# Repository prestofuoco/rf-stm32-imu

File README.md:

# rf-stm32-imu
4-layer (sig-gnd-gnd-sig) PCB with STM32F4, ICM20948, NRF24L01, USB-C, and 2.4GHz PCB trace antenna from TI's AN043. USB and RF traces are impedance matched/controlled to 90 ohms and 50 ohms respectively.

Antenna: https://www.ti.com/lit/an/swra117d/swra117d.pdf

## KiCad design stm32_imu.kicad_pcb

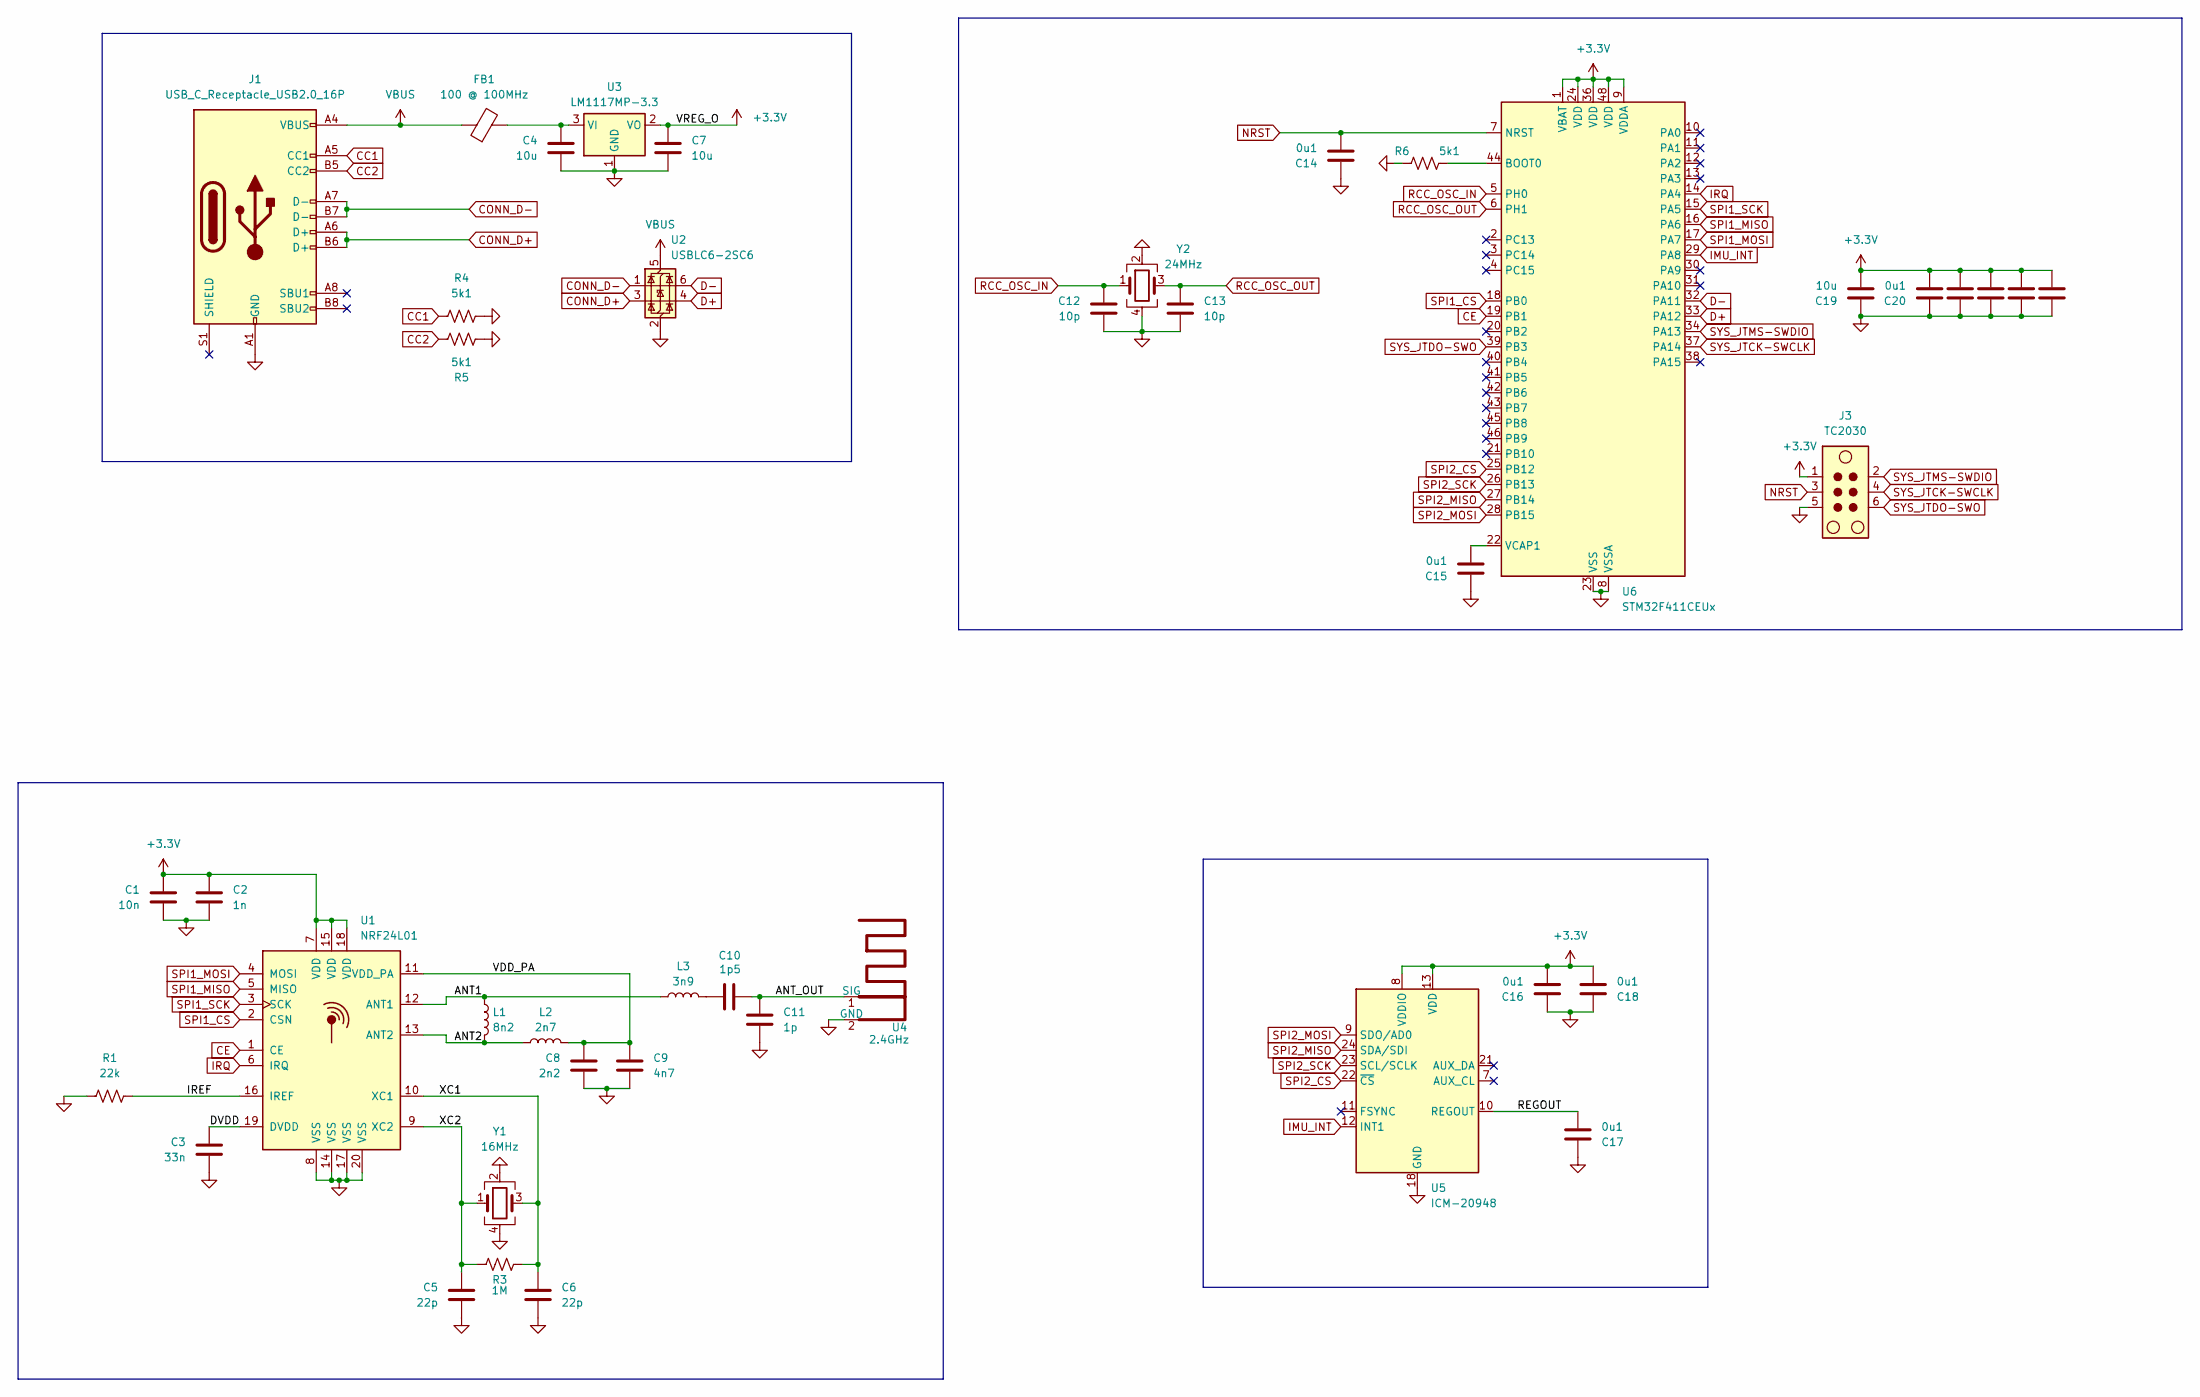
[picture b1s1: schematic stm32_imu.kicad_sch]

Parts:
C1: 10n; C_0402_1005Metric
C2: 1n; C_0402_1005Metric
C3: 33n; C_0402_1005Metric
C4, C7, C19: 10u; C_0603_1608Metric
C5, C6: 22p; C_0402_1005Metric
C8: 2n2; C_0402_1005Metric
C9: 4n7; C_0402_1005Metric
C10: 1p5; C_0402_1005Metric
C11: 1p; C_0402_1005Metric
C12, C13: 10p; C_0402_1005Metric
C14, C15, C16, C17, C18, C20, C21, C22, C23, C24: 0u1; C_0402_1005Metric
FB1: 100 @ 100MHz; L_0603_1608Metric
J1: USB_C_Receptacle_USB2.0_16P; USB_C_Receptacle_GCT_USB4085
J3: TC2030; Tag-Connect_TC2030-IDC-NL_2x03_P1.27mm_Vertical
L1: 8n2; L_0402_1005Metric
L2: 2n7; L_0402_1005Metric
L3: 3n9; L_0402_1005Metric
R1: 22k; R_0402_1005Metric
R3: 1M; R_0402_1005Metric
R4, R5, R6: 5k1; R_0402_1005Metric
U1: NRF24L01; QFN-20-1EP_4x4mm_P0.5mm_EP2.5x2.5mm
U2: USBLC6-2SC6; SOT-23-6
U3: LM1117MP-3.3; SOT-223-3_TabPin2
U4: 2.4GHz; Untitled
U5: ICM-20948; QFN-24-1EP_3x3mm_P0.4mm_EP1.75x1.6mm
U6: STM32F411CEUx; QFN-48-1EP_7x7mm_P0.5mm_EP5.15x5.15mm_ThermalVias
Y1: 16MHz; Crystal_SMD_EuroQuartz_MT-4Pin_3.2x2.5mm
Y2: 24MHz; Crystal_SMD_Abracon_ABM8G-4Pin_3.2x2.5mm

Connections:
+3.3V: C1.1, C2.1, C7.1, C16.2, C18.2, C19.2, C20.2, C21.2, C22.2, C23.2, C24.2, J3.1, U1.7 (VDD), U1.15 (VDD), U1.18 (VDD), U3.2 (VO), U5.8 (VDDIO), U5.13 (VDD), U6.1 (VBAT), U6.9 (VDDA), U6.24 (VDD), U6.36 (VDD), U6.48 (VDD)
/ANT1: L1.1, L3.1, U1.12 (ANT1)
/ANT2: L1.2, L2.1, U1.13 (ANT2)
/ANT_OUT: C10.2, C11.1, U4.1 (SIG)
/DVDD: C3.1, U1.19 (DVDD)
/IREF: R1.2, U1.16 (IREF)
/REGOUT: C17.2, U5.10 (REGOUT)
/VDD_PA: C8.1, C9.1, L2.2, U1.11 (VDD_PA)
/XC1: C6.1, R3.1, U1.10 (XC1), Y1.3
/XC2: C5.1, R3.2, U1.9 (XC2), Y1.1
CC1: J1.A5 (CC1), R4.1
CC2: J1.B5 (CC2), R5.2
CE: U1.1 (CE), U6.19 (PB1)
CONN_D+: J1.A6 (D+), J1.B6 (D+), U2.3 (I/O2)
CONN_D-: J1.A7 (D-), J1.B7 (D-), U2.1 (I/O1)
D+: U2.4 (I/O2), U6.33 (PA12)
D-: U2.6 (I/O1), U6.32 (PA11)
GND: C1.2, C2.2, C3.2, C4.2, C5.2, C6.2, C7.2, C8.2, C9.2, C11.2, C12.2, C13.2, C14.1, C15.1, C16.1, C17.1, C18.1, C19.1, C20.1, C21.1, C22.1, C23.1, C24.1, J1.A1 (GND), J1.A12 (GND), J1.B1 (GND), J1.B12 (GND), J3.5, R1.1, R4.2, R5.1, R6.1, U1.8 (VSS), U1.14 (VSS), U1.17 (VSS), U1.20 (VSS), U2.2 (GND), U3.1 (GND), U4.2 (GND), U5.18 (GND), U5.20 (GND), U6.8 (VSSA), U6.23 (VSS), U6.35 (VSS), U6.47 (VSS), U6.49 (VSS), Y1.2, Y1.4, Y2.2, Y2.4
IMU_INT: U5.12 (INT1), U6.29 (PA8)
IRQ: U1.6 (IRQ), U6.14 (PA4)
NRST: C14.2, J3.3, U6.7 (NRST)
unnamed: C10.1, L3.2
unnamed: C4.1, FB1.2, U3.3 (VI)
unnamed: R6.2, U6.44 (BOOT0)
unnamed: C15.2, U6.22 (VCAP1)
RCC_OSC_IN: C12.1, U6.5 (PH0), Y2.1
RCC_OSC_OUT: C13.1, U6.6 (PH1), Y2.3
SPI1_CS: U1.2 (CSN), U6.18 (PB0)
SPI1_MISO: U1.5 (MISO), U6.16 (PA6)
SPI1_MOSI: U1.4 (MOSI), U6.17 (PA7)
SPI1_SCK: U1.3 (SCK), U6.15 (PA5)
SPI2_CS: U5.22 (~CS), U6.25 (PB12)
SPI2_MISO: U5.24 (SDA/SDI), U6.27 (PB14)
SPI2_MOSI: U5.9 (SDO/AD0), U6.28 (PB15)
SPI2_SCK: U5.23 (SCL/SCLK), U6.26 (PB13)
SYS_JTCK-SWCLK: J3.4, U6.37 (PA14)
SYS_JTDO-SWO: J3.6, U6.39 (PB3)
SYS_JTMS-SWDIO: J3.2, U6.34 (PA13)
VBUS: FB1.1, J1.A4 (VBUS), J1.A9 (VBUS), J1.B4 (VBUS), J1.B9 (VBUS), U2.5 (VBUS)

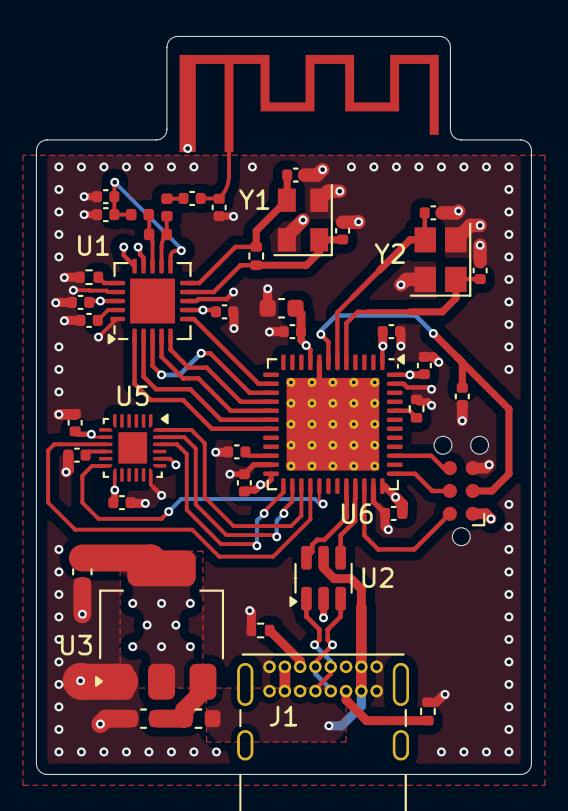
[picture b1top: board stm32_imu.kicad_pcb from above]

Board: 4 copper layers, 27.5 x 41.0 mm, 43 parts (0 on the bottom side), 39 nets.

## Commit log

2026-01-04 edited layout
